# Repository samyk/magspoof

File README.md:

# [MagSpoof](http://samy.pl/magspoof/) - credit card/magstripe spoofer
* Allows you to store all of your credit cards and magstripes in one device
* Works on traditional magstripe readers **wirelessly** (no NFC/RFID required)
* Can **disable** Chip-and-PIN (code not included)
* Correctly **predicts** Amex credit card numbers + expirations from previous card number (code not included)
* Supports all three magnetic stripe tracks, and even supports Track 1+2 simultaneously
* Easy to build using Arduino or other common parts

**[MagSpoof](http://samy.pl/magspoof)** is a device that can spoof/emulate any magnetic stripe or credit card. It can work "wirelessly", even on **standard magstripe/credit card readers**, by generating a strong electromagnetic field that emulates a traditional magnetic stripe card.

**Note:** MagSpoof does **not** enable you to use credit cards that you are not legally authorized to use. The Chip-and-PIN and Amex information is **not** implemented and using MagSpoof requires you to have/own the magstripes that you wish to emulate. Simply having a credit card number and expiration is not enough to perform transactions. MagSpoof **does** allow you to perform research in other areas of magstripes, microcontrollers, and electromagnetism, as well as learn about and create your own devices similar to other existing, commercial technologies such as <a href="http://www.samsung.com/us/support/answer/ANS00043865/997410383/">Samsung MST</a> and <a href="https://onlycoin.com/">Coin</a>.</p>

MagSpoof can be used as a traditional credit card and simply store all of your credit cards (and with modification, can technically disable chip requirements) in various impressive and exciting form factors, or can be used for security research in any area that would traditionally require a magstripe, such as readers for credit cards, drivers licenses, hotel room keys, automated parking lot tickets, etc.

**Live demonstration** and more details available in the video:

**Point of Contact:** [@SamyKamkar](https://twitter.com/samykamkar) // <code@samy.pl> // <http://samy.pl>

**Released:** November 24, 2015

**Source code / schematic:** [https://github.com/samyk/magspoof](https://github.com/samyk/magspoof)

-----

# How magnetic stripes work

Magnetic stripes (magstripes) are in fact magnetic. What's so cool about magstripes is that while the magnetic strips inside are weak, they're still strong enough to attract small ferrous particles and wide enough that we can **fully extract all data from a magstripe or credit card with the naked eye**. 

In the video, I actually dip my credit card into a bag of iron oxide. The magnetic elements in the magstripe attract the iron oxide and after pulling it out, you can actually see each bit in the tracks. [Financial cards](https://en.wikipedia.org/wiki/Magnetic_stripe_card#Financial_cards) with magnetic strips can have up to three tracks, however credit cards only have two tracks (Tracks 1 and 2). Track 2 stores fewer bits than Track 1, so it has a lower linear density (bits per inch).  This makes Track 2 much easier to see. Let's take a look:

Front of card:

As you can see on my card, I've written out the bits above the strips. Two solid stripes is a 1 and a stripe followed by a space is a 0. First, let's flip the card 180 degrees (looking at it upside down), and read it as least significant bit first. We ignore all the initial 0's until the very first 1.

Track 2 is 5 bits per character, least significant bit first, and the 5th bit is an odd parity bit. By taking each 5 bits and reading the first 4 bits, we can now begin extracting the credit card number (and other data, such as expiration date, discretionary data, CVV/CVC/CSC/CID/CAV depending on card type).

Note that the CVV is different than the CVV2. The CVV is stored on the magstripe, while the CVV2 is printed on a card. (CVV is specific to Visa, and each issuer has their own name such as CSC, CVC, etc.)

------

# How MagSpoof Works

MagSpoof emulates a magnetic stripe by quickly changing the polarization of an electromagnet, producing a magnetic field similar to that of a normal magnetic stripe as if it's being swiped. What's incredible is that the magstripe reader requires no form of wireless receiver, NFC, or RFID -- MagSpoof works wirelessly, even with **standard magstripe readers.** The stronger the electromagnet, the further away you can use it (a few inches in its current iteration).

MagSpoof also uses inexpensive, off the shelf parts (described in the Hardware section), and can be built with almost nothing more than an Arduino, wire and a battery! I use a motor driver to provide a reasonable amount of power.

Normally electromagnets have an iron core, however we lose the core for the sake of space and portability. Also, while the iron core does make the electromagnet more efficient, we still produce more than enough power to work.

**MagSpoof improves on new cards such as Coin.** I'm a customer of Coin, and while I love their app and the card, the card actually works a very small percentage of the time. After looking over Coin's FCC docs, I noticed they use two coils to produce a (very small) electromagnetic field, however it's severely deficient and the card works less than 50% of the time for me, sadly.

I found that by emulating a card with MagSpoof, if I send Track 1 one way, and then send Track 2 reversed, every card reader will assume I simply swiped a card back and forth, use the data from both tracks and my strong electromagnet, and properly read all of the data. This is extremely effective, uses only a single coil, and works for both tracks simultaneously. This also allows MagSpoof to work on Track 3.

Additionally, if you're using a Chip card with Coin, you **still** need to bring your actual credit card to dip, however because MagSpoof can disable Chip-and-PIN (see below), it does **not** require you to bring your card with you.

I've removed the Chip-and-PIN disabling functionality from MagSpoof.

-----

# Security Issues

One of the primary issues I've found is that some of the new forms of security (well, new in the US) are set in the "service code" portion of the magstripe, most specifically **Chip-and-PIN.**

The service code within a credit card magstripe defines several attributes of the card, including whether the card can dispense cash, where it can work (nationally, internationally), and most interestingly, whether the card has a built in IC (Chip) and if it has a pin (Chip-and-PIN / EMV).

If your card has a chip inside and you go to a retailer that supports Chip but swipe just your magstripe, the point of sale (PoS) system will ask you to dip your card/chip for additional security if it supports it.

**However, the bits stating the card has Chip-and-PIN can be turned off from the magstripe.** This means if you take a card to a retailer that would normally request you to dip, you can actually get away with not dipping your chip at all while performing a successful transaction, **evading the security measures altogether**.

------

# American Express Card Number Prediction

What initially led me to investigate magnetic stripes was my Amex card. After losing a card and Amex quickly sending me a replacement, I noticed many of the digits were similar. I pulled up the numbers to several other Amex cards I had, and then compared against more than 20 other Amex cards and replacements and found **a global pattern that allows me to accurately predict American Express card numbers by knowing a full card number, even if already reported lost or stolen.**

This means if I were to obtain your Amex card and you called it in as lost or stolen, the moment you get a new card, I know your new credit card number.

I also know the new expiration date as the expiration date is fixed based on when the new card was requested, and you can determine if the new card has been requested by performing an auth on the existing card.

The CID (aka CVV2 on Visa) printed on the card is protected by a secret 3DES key that encrypts the PAN (Primary Account Number, aka credit card number), service code (see above), and expiration. The service code can be easily determined as most cards will contain the same service code.

I also determined that the CSC (essentially behaves like a CID or CVV2 on the magstripe) for a lost or stolen card **continues to work** for a newer, predicted card. An attacker would be able to use a stolen card's CSC with the predicted card number and expiration to make actual purchases.

To actually perform the transaction without arousing suspicion, an attacker would be able to use a magstripe writer (e.g., the well known MSR605), or a device like MagSpoof, to "load" the newly devised card information onto a card like Coin. Coin itself does not actually verify the CID (CVV2), thus allowing an attacker to load data, and then use the Coin card in person without knowing the CID and exploiting these various issues, as well as disabling Chip-and-PIN.

I notified American Express of the issue and I will not be releasing their algorithm.

-----

# Hardware

### [Atmel ATtiny85](http://amzn.to/1S3ha9s) (microcontroller)
An Atmel ATtiny85 is the microcontroller to drive the entire system. It stores all of the magnetic stripe / credit card data. In a thinner, credit-card sized (0.8mm thick!) version, I use an [ATtiny10].

### [L293D H-Bridge](http://amzn.to/1S3h9Ck) (motor driver)
I use an L293D H-bridge to drive the electromagnet. The L293D is a motor driver, but motors are actually driven by the electromagnet(s) and magnets inside of them. Any standard driver should work here. Technically the L293D doesn't work down at 3.7V (voltage of the LiPo battery), but it works surprisingly well. In the credit-card size version, I suggest using a the TI DRV8835 or [TI DRV8833](http://amzn.to/1lu0bTd).

### [24AWG Magnet Wire](http://amzn.to/1lu0ihK) (coil)
I use somewhere around ~24AWG magnet wire to act as the coil to produce the electromagnetic field. This piece of wire incredibly produces an electromagnetic field that makes the card reader believe a card is being swiped. Incredible. By rapidly controlling the polarization of this field, the magstripe reader believes the flipped bits of a real card are being swiped through the reader.

### [100mAh 3.7V LiPo battery](http://amzn.to/1S3h69E) (the powah)
A small 100mAh 3.7V lipo battery powers our contraption. For the credit card size version (not shown here), I use a battery from [PowerStream](http://www.powerstream.com/thin-lithium-ion.htm).

#### [100µF Capacitor](http://amzn.to/1MAONOc)
Keep enough energy in this capacitor to provide the electromagnet with power when we need it, otherwise it will pull too much current and reset the microcontroller. This is the capacitor kit I use as it has all the standard values I'd need.

#### [LED](http://amzn.to/1Hl3y8Z)
To signal to us when we transmit information. I use this LED kit as it has a nice variety of LEDs.

#### [100Ω Resistor](http://amzn.to/1IeCMtP)
Don't burn out the LED.

#### [Momentary Switch](http://amzn.to/1Hl3R3T)
Initiate the electromagnet.

#### [Mini-Protoboard](http://amzn.to/1Hl3VQV)
For soldering everything together.

-----

# Firmware

### MagSpoof
MagSpoof's source code and schematic can be obtained in entirety from my github: <https://github.com/samyk/magspoof>

MagSpoof is compatible with the Arduino framework and can work on traditional Arduinos as well as ATtiny chips.

-----
# Resources

You can learn about magnetic stripes and credit cards from a few places, including:

* [My video on MagSpoof](https://www.youtube.com/watch?v=UHSFf0Lz1qc)
* [ISO/IEC 7810](https://en.wikipedia.org/wiki/ISO/IEC_7810)
* [ISO/IEC 7811](https://en.wikipedia.org/wiki/ISO/IEC_7811)
* [ISO/IEC 7812](https://en.wikipedia.org/wiki/ISO/IEC_7812)
* [ISO/IEC 7813](https://en.wikipedia.org/wiki/ISO/IEC_7813)
* [ISO 8583](https://en.wikipedia.org/wiki/ISO_8583)
* [ISO/IEC 4909](https://en.wikipedia.org/wiki/ISO/IEC_4909)
* [MagTek Magnetic Stripe Standards](http://www.magtek.com/documentation/public/99800004-1.08.pdf) (pdf)
* [Magnetic Stripe Card on Wikipedia](https://en.wikipedia.org/wiki/Magnetic_stripe_card)
* [Amex's Web Services Plural Interface](http://secure.cmax.americanexpress.com/Internet/MSWS/English/PIP-XML_Oct2010.pdf)

-----

# Contact

**Point of Contact:** [@SamyKamkar](https://twitter.com/samykamkar)

You can see more of my projects at <http://samy.pl> or contact me at <code@samy.pl>.

------

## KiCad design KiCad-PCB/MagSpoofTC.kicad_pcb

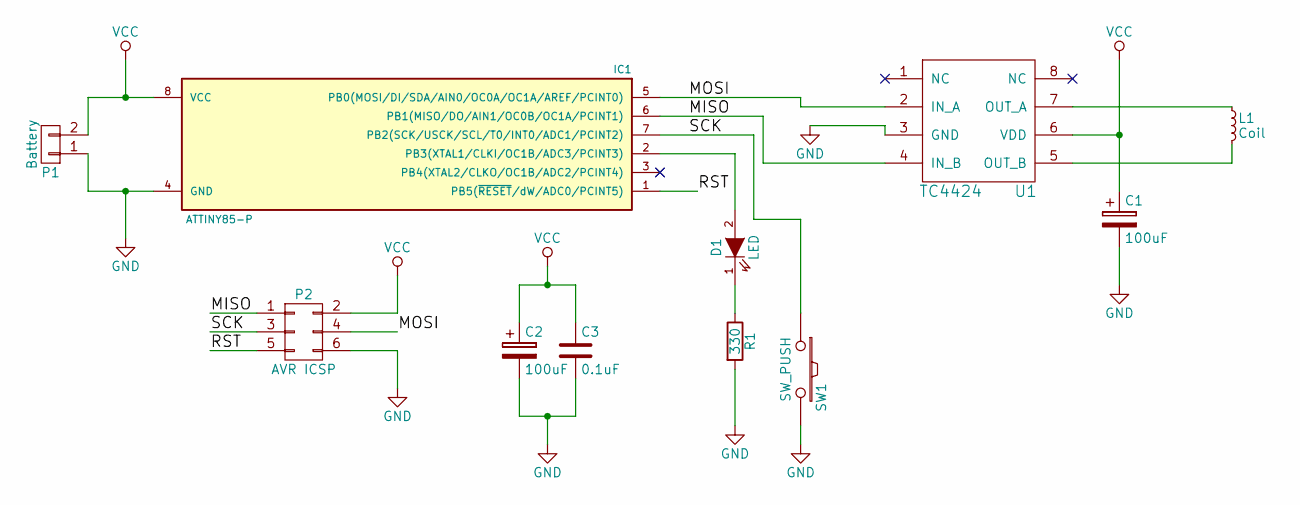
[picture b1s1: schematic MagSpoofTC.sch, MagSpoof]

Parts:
C1, C2: 100uF; 1411(3528m)-B%2CM%2CH%2CT-TANTALUM
C3: 0.1uF; C_0603_HandSoldering
D1: LED; LED-0805
IC1: ATTINY85-P; DIP-8_W7.62mm_LongPads
L1: Coil; Resistor_Horizontal_RM10mm
P1: Battery; Pin_Header_Straight_1x02
P2: AVR ICSP; Pin_Header_Straight_2x03
R1: 330; R_0603_HandSoldering
SW1: SW_PUSH; SW_PUSH_SMD
U1: TC4424; DIP-8_W7.62mm_LongPads

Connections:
/MISO: IC1.6 (PB1(MISO/DO/AIN1/OC0B/OC1A/PCINT1)), P2.1, U1.4 (IN_B)
/MOSI: IC1.5 (PB0(MOSI/DI/SDA/AIN0/OC0A/OC1A/AREF/PCI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), P2.4, U1.2 (IN_A)
/RST: IC1.1 (PB5(~RESET~/dW/ADC0/PCINT5)), P2.5
/SCK: IC1.7 (PB2(SCK/USCK/SCL/T0/INT0/ADC1/PCINT2)), P2.3, SW1.1
GND: C1.2, C2.2, C3.2, IC1.4 (GND), P1.1, P2.6, R1.2, SW1.2, U1.3 (GND)
unnamed: D1.1 (K), R1.1
unnamed: D1.2 (A), IC1.2 (PB3(XTAL1/CLKI/OC1B/ADC3/PCINT3))
unnamed: L1.1, U1.7 (OUT_A)
unnamed: L1.2, U1.5 (OUT_B)
VCC: C1.1, C2.1, C3.1, IC1.8 (VCC), P1.2, P2.2, U1.6 (VDD)

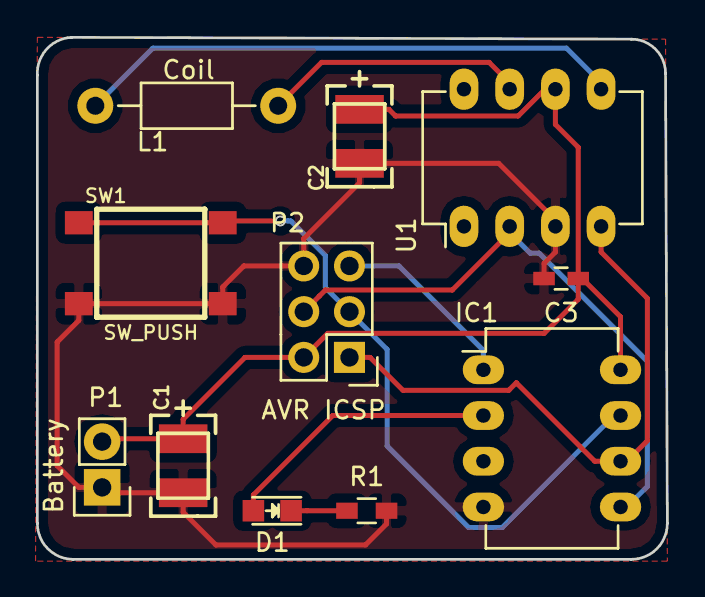
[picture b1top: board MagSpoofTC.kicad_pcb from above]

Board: 2 copper layers, 35.0 x 29.0 mm, 11 parts (0 on the bottom side), 10 nets.

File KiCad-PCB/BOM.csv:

Reference, Value, Footprint, Datasheet, Manufacturer, Temperatura, Alimentacion, Description
IC1,ATTINY85-P,Housings_DIP:DIP-8_W7.62mm_LongPads,http://www.farnell.com/datasheets/1744708.pdf,ATMEL,+85/-40,5v,ATMEL 	ATTINY85-20PU  Microcontrolador 8 Bits, Baja Potencia, Alto Rendimiento, ATtiny, 20 MHz, 8 KB, 500 Byte, 8 Pines
D1,LED,LEDs:LED-0805,,Maxim,+85/-40,5v,Led red 0805
L1,Coil,Resistors_ThroughHole:Resistor_Horizontal_RM10mm,
R1,330,Resistors_SMD:R_0603_HandSoldering,,,+85/-40,5v,Resistor 330ohms
C1,100uF,theinventorhouse:1411(3528m)-B%2CM%2CH%2CT-TANTALUM,http://www.farnell.com/datasheets/1923743.pdf,Kemet,+85/-40,6.3v,KEMET 	T520T107M006ATE070  CAP, TANT, POLYMER, 100UF, 6.3V, 1411
SW1,SW_PUSH,open-project:SW_PUSH_SMD,
P2,AVR ICSP,Pin_Headers:Pin_Header_Straight_2x03,,Maxim,+85/-40,5v,
P1,Battery,Pin_Headers:Pin_Header_Straight_1x02,
C3,0.1uF,Capacitors_SMD:C_0603_HandSoldering,http://www.farnell.com/datasheets/2009679.pdf,WALSIN,+85/-40,50v,WALSIN 	0603F104Z500CT  CAP, MLCC, Y5V, 0.1UF, 50V, 0603, REEL
U1,TC4424,Housings_DIP:DIP-8_W7.62mm_LongPads,http://www.farnell.com/datasheets/95980.pdf,Microchip,+85/-40,2.7-5v,MICROCHIP 	TC4424CPA  MOSFET Driver Lado Bajo, Alimentación:4.5-18V, Salida Pico:3A, Salida:3.5 Ohm, DIP-
C2,100uF,theinventorhouse:1411(3528m)-B%2CM%2CH%2CT-TANTALUM,http://www.farnell.com/datasheets/1923743.pdf,Kemet,+85/-40,6.3v,KEMET 	T520T107M006ATE070  CAP, TANT, POLYMER, 100UF, 6.3V, 1411

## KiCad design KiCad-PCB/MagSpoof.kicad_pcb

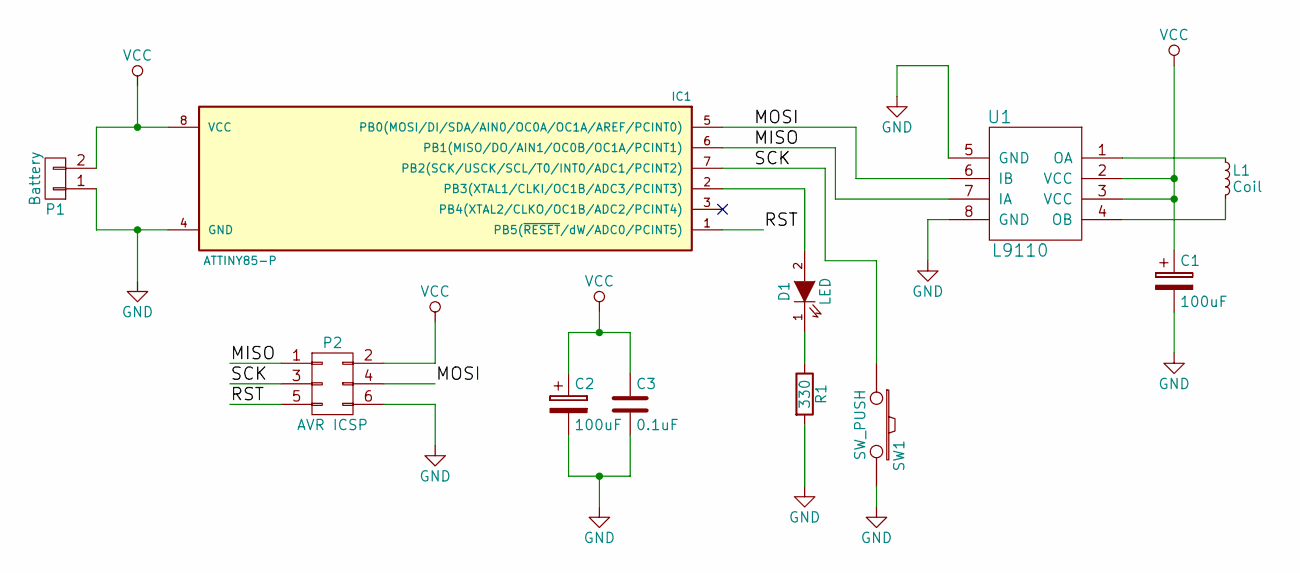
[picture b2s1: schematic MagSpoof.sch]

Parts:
C1, C2: 100uF; 1411(3528m)-B%2CM%2CH%2CT-TANTALUM
C3: 0.1uF; C_0805_HandSoldering
D1: LED; LED-0805
IC1: ATTINY85-P; DIP-8_W7.62mm_LongPads
L1: Coil; Resistor_Horizontal_RM10mm
P1: Battery; Pin_Header_Straight_1x02
P2: AVR ICSP; Pin_Header_Straight_2x03
R1: 330; R_0805_HandSoldering
SW1: SW_PUSH; SW_PUSH_SMD
U1: L9110; DIP-8_W7.62mm_LongPads

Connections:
/MISO: IC1.6 (PB1(MISO/DO/AIN1/OC0B/OC1A/PCINT1)), P2.1, U1.7 (IA)
/MOSI: IC1.5 (PB0(MOSI/DI/SDA/AIN0/OC0A/OC1A/AREF/PCI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), P2.4, U1.6 (IB)
/RST: IC1.1 (PB5(~RESET~/dW/ADC0/PCINT5)), P2.5
/SCK: IC1.7 (PB2(SCK/USCK/SCL/T0/INT0/ADC1/PCINT2)), P2.3, SW1.1
GND: C1.2, C2.2, C3.2, IC1.4 (GND), P1.1, P2.6, R1.2, SW1.2, U1.5 (GND), U1.8 (GND)
unnamed: D1.1 (K), R1.1
unnamed: D1.2 (A), IC1.2 (PB3(XTAL1/CLKI/OC1B/ADC3/PCINT3))
unnamed: L1.1, U1.1 (OA)
unnamed: L1.2, U1.4 (OB)
VCC: C1.1, C2.1, C3.1, IC1.8 (VCC), P1.2, P2.2, U1.2 (VCC), U1.3 (VCC)

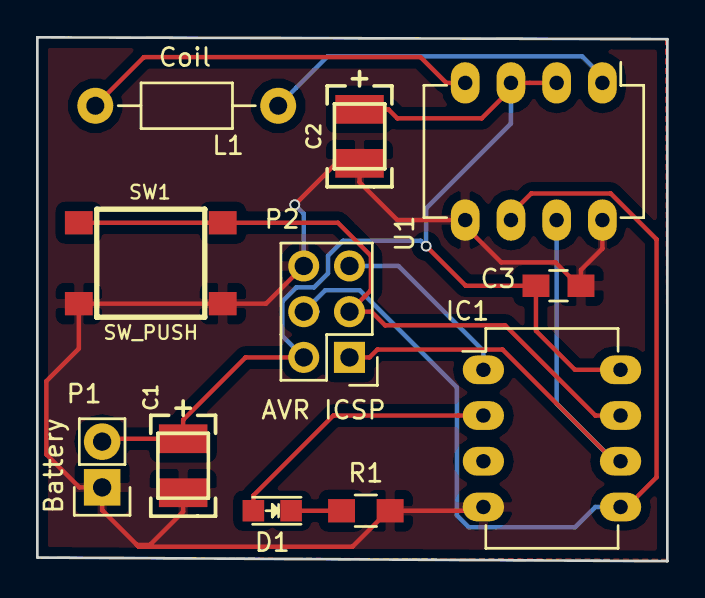
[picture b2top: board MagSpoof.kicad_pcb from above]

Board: 2 copper layers, 35.0 x 29.1 mm, 12 parts (1 on the bottom side), 10 nets.

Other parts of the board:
Electroniccats: OSHW-Logo; Symbol_OSHW-Logo_SilkScreen

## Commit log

2015-11-24 First release of MagSpoof, wireless magstripe/credit card spoofer/emulator
2015-11-24 added rest of the circuit
2015-11-25 Added Eagle schematic file
2015-11-25 README: clarify description of track1/2 diffs
    Also, include link to wikipedia page.
2015-11-25 Fix a couple of numeric units
2015-11-25 implemented chip-and-pin bypass
2015-11-25 README updated to replect chip-and-pin bypass functionality
2015-11-25 Updated README to reflect chip-and-pin bypass addition
2016-01-05 Fixed wrong pin connection, PB4->PB3 (thanks @shellster)
2016-01-08 Update README to use correct schematic rendering
    The image was updated in commit: https://github.com/samyk/magspoof/commit/f7f1d3c868b5509da58ddc3946a1869d8c942584
    but not updated in the README so it was difficult to find.
2016-01-20 Add Schematic and PCB in Kicad
2016-06-25 New version with TC4424
2016-06-25 New version with TC4424 Kicad
2016-06-25 Add RenderBoard
2016-06-25 Add BOM
2016-06-25 Default CC
2016-08-27 fixes #12
2016-10-08 Added Blind Public License
2016-10-08 Added Blind Public License (BPL)
2016-10-08 Updated Blind Public License
2016-10-08 further specifications added to license
2017-01-11 Delete LICENSE-BPL.md
    hey this is crazy so remove the license maybe
2019-01-30 Fix BOM CSV
    Quote some lines and add commas to make the rows the same size, and remove the spanish headings
2022-07-03 Update BOM.csv
    Add columns for both English and Spanish languages.
